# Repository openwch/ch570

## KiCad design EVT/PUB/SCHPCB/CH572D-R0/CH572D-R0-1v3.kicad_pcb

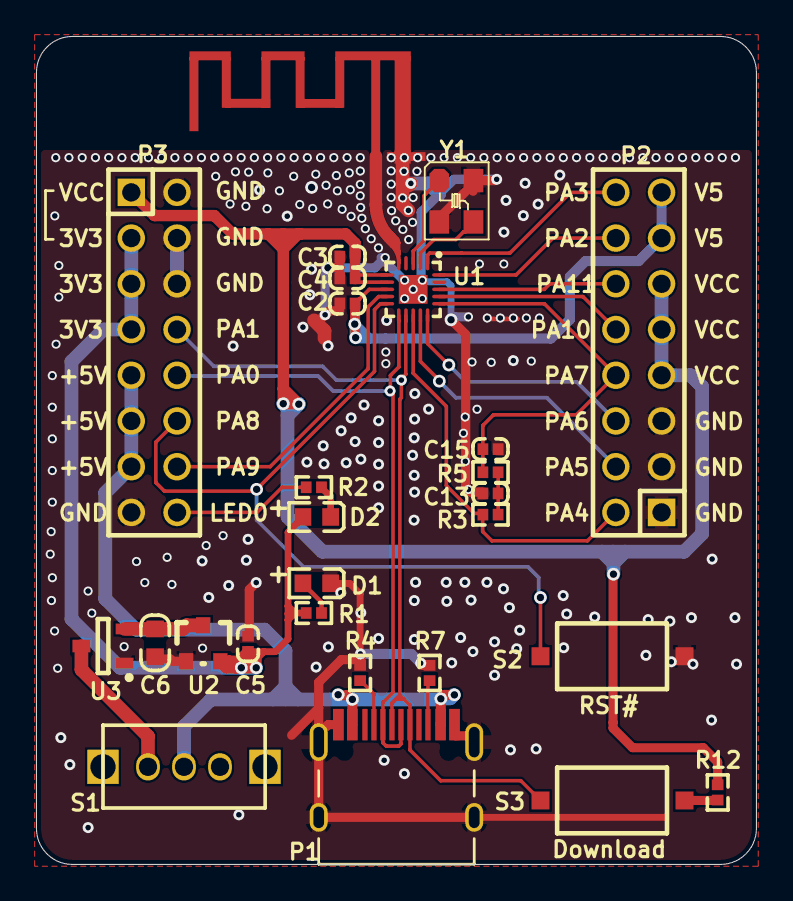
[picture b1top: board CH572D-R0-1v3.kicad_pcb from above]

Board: 2 copper layers, 40.0 x 46.0 mm, 27 parts (0 on the bottom side), 29 nets.

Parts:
C2, C3, C5: 2.2uF; 0402_C
C4: 0.1uF; 0402_C
C6: 10uF; 0603_C
C13, C15: NC(10nF); 0402_C
D1: POWER; 0603+
D2: LED0; 0603+
E1: ANTENNA; ANT-F-1-2.4G-1.6mmFR4
P1: TYPE-C-Receptacle-2.0
P2, P3: HEADER 8x2; IDC16-2.54mm
R1, R2: 1K; 0402
R3, R5: NC(2.2K); 0402
R4, R7, R12: 5.1K; 0402
S1: SW; SW1
S2: RST#; SMD_6.1x3.65x2.5mm-KEY
S3: Download; SMD_6.1x3.65x2.5mm-KEY
U1: CH572D; QFN20_3X3
U2: 6219P33M; SOT-23
U3: CH213E; SOT-23-3
Y1: 32MHz; XT3225

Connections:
+3V3: C5.2, D2.1, P3.3, P3.5, P3.7, R1.2, U2.2
+5V: P1.A4, P1.B4, P3.9, P3.11, P3.13, S1.1
ANT: E1.1, U1.5
BOOT: P1.A6, P1.B6, P3.8, S3.2, U1.12
GND: C2.2, C3.2, C4.2, C5.1, C6.2, C13.2, C15.2, D1.2, E1.0, P1.0, P1.A1, P1.B1, P2.1, P2.3, P2.5, P3.2, P3.4, P3.6, P3.15, R4.2, R7.1, S2.1, U1.0, U2.1, U3.1, Y1.2, Y1.4
LED0: P3.16, R2.1
NetC6_1: C6.1, U2.3, U3.2
NetC13_1: C13.1, R3.2, R5.1
NetD1_1: D1.1, R1.1
NetD2_2: D2.2, R2.2
NetP1_A5: P1.A5, R4.1
NetP1_B5: P1.B5, R7.2
NetR12_1: R12.1, S3.1
NetS1_3: S1.3, U3.3
PA0: P1.A7, P1.B7, P3.10, U1.11
PA2: P2.14, U1.20
PA3: P2.16, U1.1
PA4: P2.2, R3.1, U1.13
PA5: P2.4, U1.14
PA6: P2.6, U1.15
PA7: C15.1, P2.8, R5.2, U1.16
PA8: P3.12, S2.2, U1.10
PA9: P3.14, U1.9
PA10: P2.10, U1.17
PA11: P2.12, U1.18
V5: C2.1, P2.13, P2.15, U1.8
VCC: C3.1, C4.1, P2.7, P2.9, P2.11, P3.1, R12.2, U1.6, U1.7
X32MI: U1.3, Y1.1
X32MO: U1.2, Y1.3

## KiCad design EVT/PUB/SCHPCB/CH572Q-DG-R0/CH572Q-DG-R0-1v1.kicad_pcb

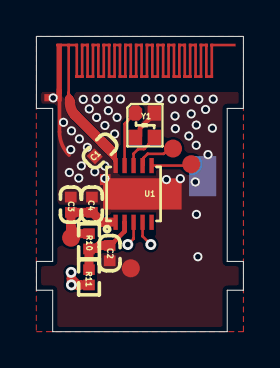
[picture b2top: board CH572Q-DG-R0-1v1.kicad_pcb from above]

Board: 2 copper layers, 11.5 x 16.4 mm, 10 parts (1 on the bottom side), 9 nets.

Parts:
C1: NC; 0402_C
C2, C3: 2.2uF; 0402_C
C4: 0.1uF; 0402_C
E1: ANTENNA; ANT-F-1-2.4G-0.8mmFR4
P3: USB; USBAM-4P
R10: 1.5K; 0402
R11: 10R; 0402
U1: CH572Q; DFN10_3X3
Y1: 32MHz; XT2016

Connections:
+5V: P3.1, R11.2
ANT: C1.1, E1.1, U1.10
GND: C1.2, C2.2, C3.2, C4.2, E1.0, P3.4, U1.0, Y1.2, Y1.4
PA0: P3.2, U1.3
PA1: P3.3, U1.4
V5: C2.1, R10.2, R11.1, U1.2
VCC: C3.1, C4.1, R10.1, U1.1
X32MI: U1.9, Y1.1
X32MO: U1.8, Y1.3

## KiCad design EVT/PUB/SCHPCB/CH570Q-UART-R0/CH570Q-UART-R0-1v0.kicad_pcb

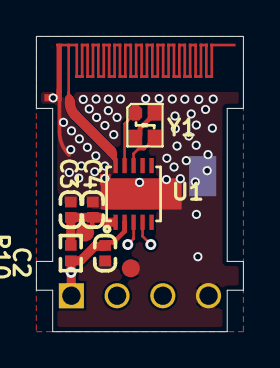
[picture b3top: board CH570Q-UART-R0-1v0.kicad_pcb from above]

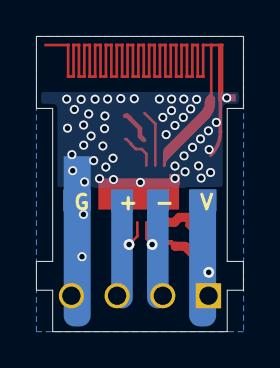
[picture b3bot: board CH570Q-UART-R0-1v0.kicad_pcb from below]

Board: 2 copper layers, 11.5 x 16.4 mm, 9 parts (2 on the bottom side), 8 nets.

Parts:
C2, C3: 2.2uF; 0402_C
C4: 0.1uF; 0402_C
E1: ANTENNA; ANT-F-1-2.4G-0.8mmFR4
P1: HEADER 4; SIP4-2.54mm
P3: USB; USBAM-4P
R10: 1.5K/0; 0402
U1: CH570Q; DFN10_3X3
Y1: 32MHz; XT2016

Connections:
ANT: E1.1, U1.10
GND: C2.2, C3.2, C4.2, E1.0, P1.4, P3.4, U1.0, Y1.2, Y1.4
PA0: P1.2, P3.2, U1.3
PA1: P1.3, P3.3, U1.4
V5: C2.1, P1.1, P3.1, R10.1, U1.2
VCC: C3.1, C4.1, R10.2, U1.1
X32MI: U1.9, Y1.1
X32MO: U1.8, Y1.3

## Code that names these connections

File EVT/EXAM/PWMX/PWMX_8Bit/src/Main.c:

/********************************** (C) COPYRIGHT *******************************
 * File Name          : Main.c
 * Author             : WCH
 * Version            : V1.1
 * Date               : 2026/09/14
 * Description        : PWMX 8位数据宽度输出例程，PWM1-5输出25%占空比波形
 *********************************************************************************
 * Copyright (c) 2021 Nanjing Qinheng Microelectronics Co., Ltd.
 * Attention: This software (modified or not) and binary are used for
 * microcontroller manufactured by Nanjing Qinheng Microelectronics.
 *******************************************************************************/

#include "CH57x_common.h"

#define PWMX_CYCLE_NUM   64

/*********************************************************************
 * @fn      DebugInit
 *
 * @brief   调试串口初始化
 *
 * @return  none
 */
void DebugInit(void)
{
    GPIOA_SetBits(bTXD_0);
    GPIOA_ModeCfg(bRXD_0, GPIO_ModeIN_PU);      // RXD-配置上拉输入
    GPIOA_ModeCfg(bTXD_0, GPIO_ModeOut_PP_5mA); // TXD-配置推挽输出，注意先让IO口输出高电平
    UART_Remap(ENABLE, UART_TX_REMAP_PA3, UART_RX_REMAP_PA2);
    UART_DefInit();
}

/*********************************************************************
 * @fn      main
 *
 * @brief   主函数
 *
 * @return  none
 */
int main(void)
{
    FlashLock();
    // 关闭两线调试
    R16_PIN_ALTERNATE &= ~RB_PIN_DEBUG_EN;
    HSECFG_Capacitance(HSECap_18p);
    SetSysClock(CLK_SOURCE_HSE_PLL_100MHz);

    /* 配置GPIO，PWM1-5默认复用引脚 */
    GPIOA_ModeCfg(GPIO_Pin_7, GPIO_ModeOut_PP_5mA); // PA7 - PWM1
    GPIOA_ModeCfg(GPIO_Pin_2, GPIO_ModeOut_PP_5mA); // PA2 - PWM2
    GPIOA_ModeCfg(GPIO_Pin_3, GPIO_ModeOut_PP_5mA); // PA3 - PWM3
    GPIOA_ModeCfg(GPIO_Pin_4, GPIO_ModeOut_PP_5mA); // PA4 - PWM4
    GPIOA_ModeCfg(GPIO_Pin_8, GPIO_ModeOut_PP_5mA); // PA8 - PWM5

    PWMX_CLKCfg(4);                // cycle = 4/Fsys
    PWMX_CycleCfg(PWMX_Cycle_64);  // 周期 = 64*cycle

    PWMX_ACTOUT(CH_PWM1, PWMX_CYCLE_NUM / 4, Low_Level, ENABLE); // 25% 占空比
    PWMX_ACTOUT(CH_PWM2, PWMX_CYCLE_NUM / 4, Low_Level, ENABLE); // 25% 占空比
    PWMX_ACTOUT(CH_PWM3, PWMX_CYCLE_NUM / 4, Low_Level, ENABLE); // 25% 占空比
    PWMX_ACTOUT(CH_PWM4, PWMX_CYCLE_NUM / 4, Low_Level, ENABLE); // 25% 占空比
    PWMX_ACTOUT(CH_PWM5, PWMX_CYCLE_NUM / 4, Low_Level, ENABLE); // 25% 占空比

    while(1);
}

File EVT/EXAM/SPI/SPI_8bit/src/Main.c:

/********************************** (C) COPYRIGHT *******************************
 * File Name          : Main.c
 * Author             : WCH
 * Version            : V1.1
 * Date               : 2026/09/15
 * Description        : SPI例程：普通模式数据收发，单字节/FIFO多字节/DMA方式，宏切换主机/从机
 *********************************************************************************
 * Copyright (c) 2021 Nanjing Qinheng Microelectronics Co., Ltd.
 * Attention: This software (modified or not) and binary are used for
 * microcontroller manufactured by Nanjing Qinheng Microelectronics.
 *******************************************************************************/

#include "CH57x_common.h"

/* 主从模式定义 */
#define SPI_MASTER_MODE     1
#define SPI_SLAVE_MODE      0

/* 主从模式选择 */
#define SPI_MODE            SPI_MASTER_MODE      // 切换模式

/* ---- 硬件引脚配置：PA4-SCS PA5-SCK PA6-MISO PA7-MOSI ---- */
#define SPI_SCS_PIN      GPIO_Pin_4
#define SPI_SCK_PIN      GPIO_Pin_5
#define SPI_MISO_PIN     GPIO_Pin_6
#define SPI_MOSI_PIN     GPIO_Pin_7

__attribute__((aligned(4))) uint8_t spiBuff[] = {1, 2, 3, 4, 5, 6, 7, 8, 9, 0, 1, 2, 3, 4, 5, 6};
__attribute__((aligned(4))) uint8_t spiBuffrev[16];

void DebugInit(void)
{
    GPIOA_SetBits(bTXD_0);
    GPIOA_ModeCfg(bRXD_0, GPIO_ModeIN_PU);      // RXD-配置上拉输入
    GPIOA_ModeCfg(bTXD_0, GPIO_ModeOut_PP_5mA); // TXD-配置推挽输出，注意先让IO口输出高电平
    UART_Remap(ENABLE, UART_TX_REMAP_PA3, UART_RX_REMAP_PA2);
    UART_DefInit();
}

int main(void)
{
    uint8_t i;

    FlashLock();
    // 关闭两线调试
    R16_PIN_ALTERNATE &= ~RB_PIN_DEBUG_EN;
    HSECFG_Capacitance(HSECap_18p);
    SetSysClock(CLK_SOURCE_HSE_PLL_100MHz);

    /* 配置串口调试 */
    DebugInit();
    PRINT("Start @ChipID=%02X\n", R8_CHIP_ID);

#if(SPI_MODE == SPI_MASTER_MODE)
    /* ---- 主机模式 ---- */
    PRINT("1.spi master mode send data ...\n");
    DelayMs(100);

    GPIOA_SetBits(SPI_SCS_PIN);
    GPIOA_ModeCfg(SPI_SCS_PIN | SPI_SCK_PIN | SPI_MOSI_PIN, GPIO_ModeOut_PP_5mA);
    SPI_MasterDefInit();

    // 单字节发送
    GPIOA_ResetBits(SPI_SCS_PIN);
    SPI_MasterSendByte(0x55);
    GPIOA_SetBits(SPI_SCS_PIN);
    DelayMs(1);
    GPIOA_ResetBits(SPI_SCS_PIN);
    i = SPI_MasterRecvByte();
    GPIOA_SetBits(SPI_SCS_PIN);
    DelayMs(2);
    PRINT("receive %x\n", i);

    // FIFO 连续发送
    GPIOA_ResetBits(SPI_SCS_PIN);
    SPI_MasterTrans(spiBuff, 8);
    GPIOA_SetBits(SPI_SCS_PIN);
    DelayMs(2);
    GPIOA_ResetBits(SPI_SCS_PIN);
    SPI_MasterRecv(spiBuffrev, 8);
    GPIOA_SetBits(SPI_SCS_PIN);
    DelayMs(2);
    PRINT("FIFO recv ");
    for(i = 0; i < 8; i++)
    {
        PRINT(" %x", spiBuffrev[i]);
    }
    PRINT("\n");

    // DMA 连续发送
    GPIOA_ResetBits(SPI_SCS_PIN);
    SPI_MasterDMATrans(spiBuff, 12);
    GPIOA_SetBits(SPI_SCS_PIN);
    DelayMs(2);
    GPIOA_ResetBits(SPI_SCS_PIN);
    SPI_MasterDMARecv(spiBuffrev, 12);
    GPIOA_SetBits(SPI_SCS_PIN);
    PRINT("DMA recv ");
    for(i = 0; i < 12; i++)
    {
        PRINT(" %x", spiBuffrev[i]);
    }
    PRINT("\n");
#else
    /* ---- 从机模式 ---- */
    PRINT("1.spi slave mode \n");
    GPIOA_ModeCfg(SPI_SCS_PIN | SPI_SCK_PIN | SPI_MISO_PIN | SPI_MOSI_PIN, GPIO_ModeIN_PU);
    SPI_SlaveInit();

    // 单字节接收与回发
    i = SPI_SlaveRecvByte();
    SPI_SlaveSendByte(0xAA);
    PRINT("receive %x\n", i);

    // FIFO 连续接收与回发
    SPI_SlaveRecv(spiBuffrev, 8);
    SPI_SlaveTrans(spiBuffrev, 8);
    PRINT("FIFO recv ");
    for(i = 0; i < 8; i++)
    {
        PRINT(" %x", spiBuffrev[i]);
    }
    PRINT("\n");

    // DMA 连续接收与回发
    SPI_SlaveDMARecv(spiBuffrev, 12);
    SPI_SlaveDMATrans(spiBuffrev, 12);
    PRINT("DMA recv ");
    for(i = 0; i < 12; i++)
    {
        PRINT(" %x", spiBuffrev[i]);
    }
    PRINT("\n");
#endif

    PRINT("END ...\n");
    while(1);
}
